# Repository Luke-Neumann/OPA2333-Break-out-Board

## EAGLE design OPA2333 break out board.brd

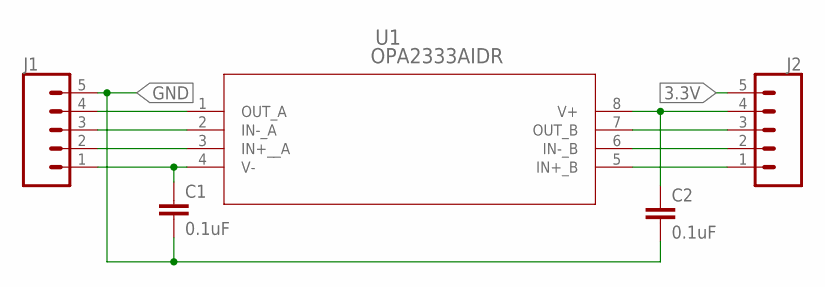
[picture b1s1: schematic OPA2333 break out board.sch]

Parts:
C1, C2: 0.1uF; 0603
J1, J2: CONN_05; 1X05
U1: OPA2333AIDR; D8

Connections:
3.3V: J2.5
GND: C1.2, C2.2, J1.5
unnamed: J1.4, U1.1 (OUT_A)
unnamed: J1.3, U1.2 (IN-_A)
unnamed: J1.2, U1.3 (IN+__A)
unnamed: C1.1, J1.1, U1.4 (V-)
unnamed: C2.1, J2.4, U1.8 (V+)
unnamed: J2.3, U1.7 (OUT_B)
unnamed: J2.2, U1.6 (IN-_B)
unnamed: J2.1, U1.5 (IN+_B)

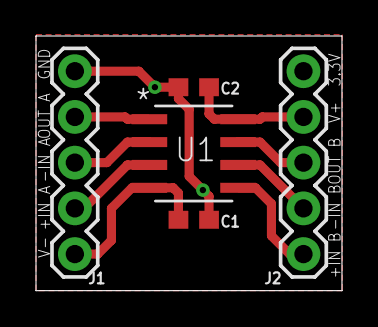
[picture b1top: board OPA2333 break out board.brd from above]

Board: 4 copper layers, 17.0 x 14.1 mm, 5 parts (0 on the bottom side), 9 nets.

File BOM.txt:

Partlist exported from /Users/lukeneumann/Documents/EAGLE/projects/OPA2333 break out board/OPA2333 break out board.sch at 5/23/19 1:38 PM

Part Value       Device                    Package Description                                                                                                     MANUFACTURER_PART_NUMBER PROD_ID   VALUE VENDOR           
C1   0.1uF       0.1UF-0603-25V-(+80/-20%) 0603    0.1µF ceramic capacitors                                                                                                                 CAP-00810 0.1uF                  
C2   0.1uF       0.1UF-0603-25V-(+80/-20%) 0603    0.1µF ceramic capacitors                                                                                                                 CAP-00810 0.1uF                  
J1               CONN_05                   1X05    Multi connection point. Often used as Generic Header-pin footprint for 0.1 inch spaced/style header connections                                                           
J2               CONN_05                   1X05    Multi connection point. Often used as Generic Header-pin footprint for 0.1 inch spaced/style header connections                                                           
U1   OPA2333AIDR OPA2333AIDR               D8                                                                                                                      OPA2333AIDR                              Texas Instruments

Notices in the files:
parts and their libraries:
SparkFun-Capacitors: Licensing: Creative Commons ShareAlike 4.0 International - https://creativecommons.org/licenses/by-sa/4.0
